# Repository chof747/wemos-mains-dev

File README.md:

## Board to combine a Wemos D1 Mini with a mini power supply

This is a small board that can take a Wemos D1 Mini  together with a 5V mini power supply to obtain a W-Lan microcontroller board with IO pins able to put e.g. in a switch box and power it
directly from mains

It contains the following elements:

- WeMos D1 Mini (or any other microcontroller board that has the same pin configuration)
- A 600mA/5V (3W) power supply 
- A 2x12 pinheader providing all GPIO Pins of the D1 mini in a suitable configuration
- Pull-Up Resistors for the SDA and SCL line
- Jumper Pins to select if the pullups should be used or not
- ByPass Capacitors for the 3V3 and GND lines in vicinity to the One-Wire and analog pin
- Screw Terminal to connect the board to mains

## Features

The breakout of the pins is designed in a way that it can support HATs of a certain form factor. So far I have designed the following HATs which you can find here:

- RJ11 Socket HAT [chof747/rj11-wemos-hat](https://github.com/chof747/rj11-wemos-hat)

## Revision History:

- **v1.0**: Initial version (filed for fabrication: 19.04.2023)
- **v1.1**: Revision 1 with corrected orientation of power supply and reduced ground plane to avoid collision with high voltage (filed for fabrication: 17.7.2023; First Assembly 06.10.2023)

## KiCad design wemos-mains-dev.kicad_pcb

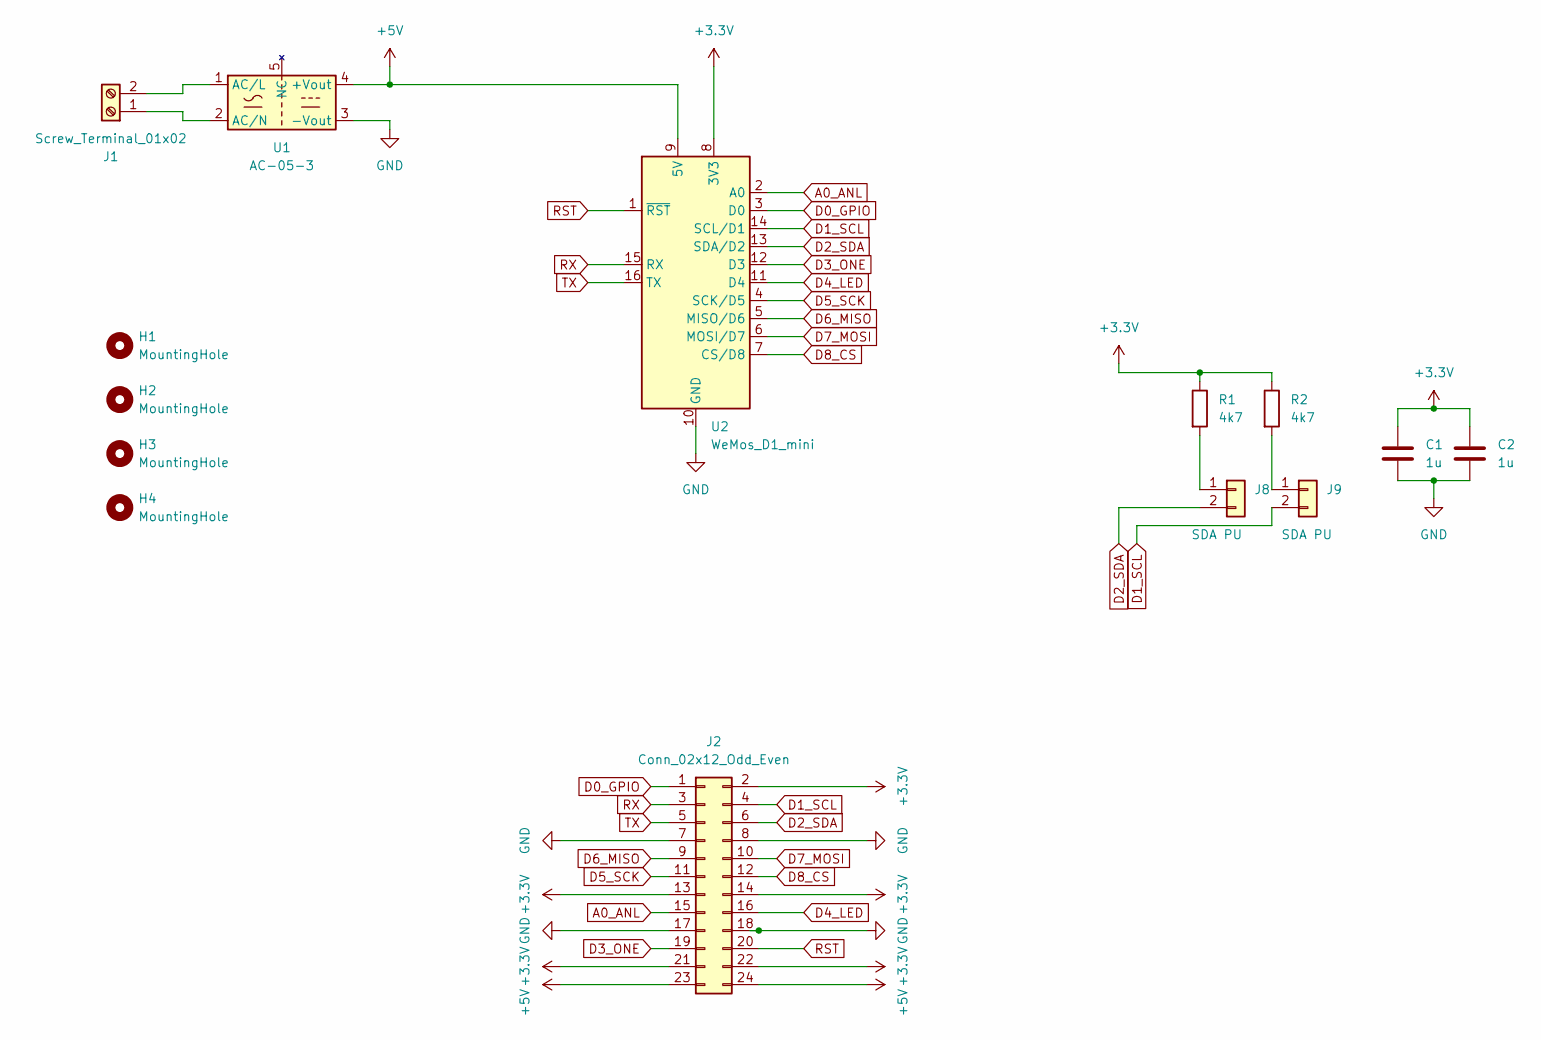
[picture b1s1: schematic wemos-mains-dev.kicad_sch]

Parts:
C1, C2: 1u; C_0603_1608Metric_Pad1.08x0.95mm_HandSolder
H1, H2, H3, H4: MountingHole; MountingHole_3.2mm_M3-smallBorder
J1: Screw_Terminal_01x02; TerminalBlock_bornier-2_P5.08mm
J2: Conn_02x12_Odd_Even; PinSocket_2x12_P2.54mm_Vertical
J8, J9: SDA PU; PinHeader_1x02_P2.54mm_Vertical
R1, R2: 4k7; R_0603_1608Metric_Pad0.98x0.95mm_HandSolder
U1: AC-05-3; AZDelivery AC-05-3
U2: WeMos_D1_mini; WEMOS_D1_mini_light

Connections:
+3.3V: C1.1, C2.1, J2.2, J2.13, J2.14, J2.21, J2.22, R1.1, R2.1, U2.8 (3V3)
+5V: J2.23, J2.24, U1.4 (+Vout), U2.9 (5V)
A0_ANL: J2.15, U2.2 (A0)
D0_GPIO: J2.1, U2.3 (D0)
D1_SCL: J2.4, J9.2, U2.14 (SCL/D1)
D2_SDA: J2.6, J8.2, U2.13 (SDA/D2)
D3_ONE: J2.19, U2.12 (D3)
D4_LED: J2.16, U2.11 (D4)
D5_SCK: J2.11, U2.4 (SCK/D5)
D6_MISO: J2.9, U2.5 (MISO/D6)
D7_MOSI: J2.10, U2.6 (MOSI/D7)
D8_CS: J2.12, U2.7 (CS/D8)
GND: C1.2, C2.2, J2.7, J2.8, J2.17, J2.18, U1.3 (-Vout), U2.10 (GND)
unnamed: J1.1, U1.2 (AC/N)
unnamed: J1.2, U1.1 (AC/L)
unnamed: J8.1, R1.2
unnamed: J9.1, R2.2
RST: J2.20, U2.1 (~RST)
RX: J2.3, U2.15 (RX)
TX: J2.5, U2.16 (TX)

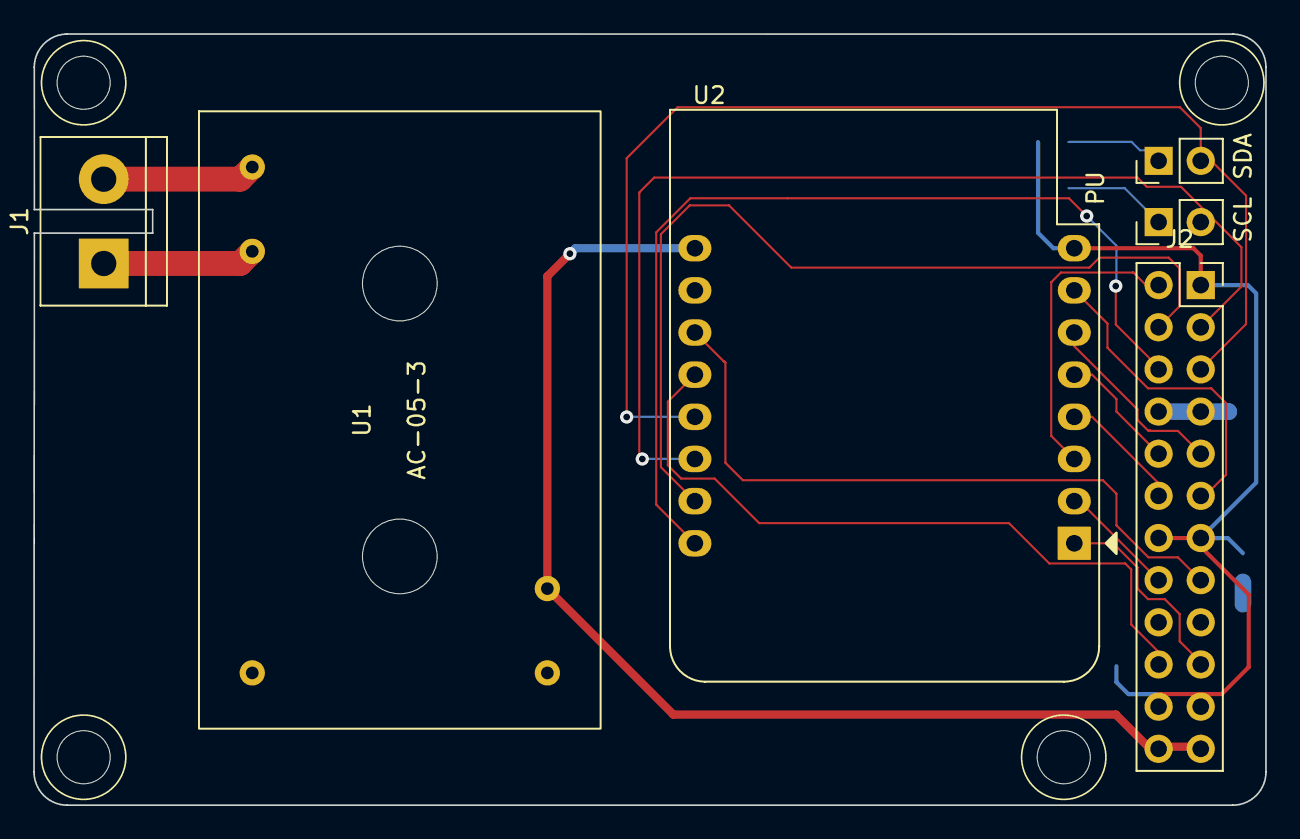
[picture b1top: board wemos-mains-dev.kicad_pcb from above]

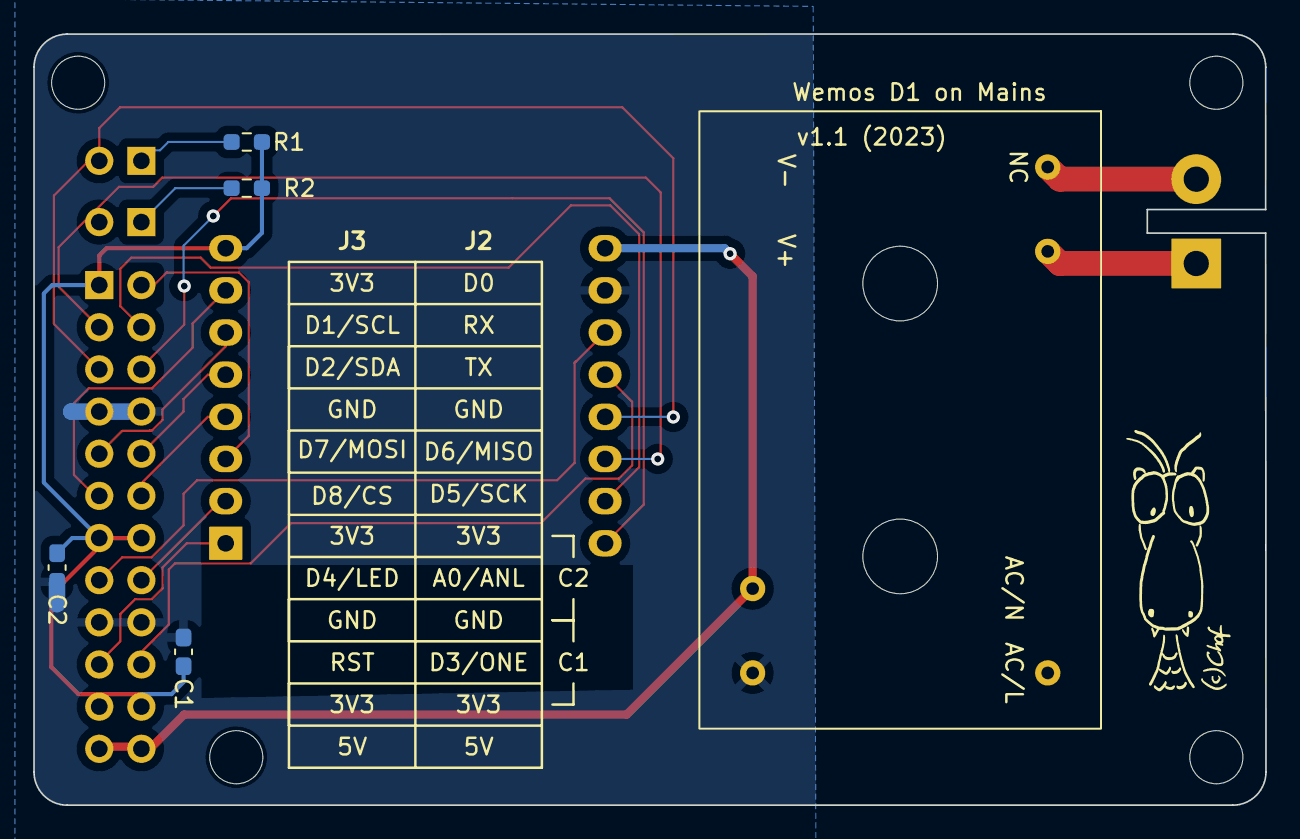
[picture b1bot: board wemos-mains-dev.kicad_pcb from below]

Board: 2 copper layers, 74.2 x 46.5 mm, 14 parts (4 on the bottom side), 20 nets.

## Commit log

2023-04-19 Version 1.0 including basic set of features for first PT board
2023-04-20 Changed pinheader for breakout to 02x12
2023-04-20 Added step file to .gitignore
2023-04-20 Revision 1 commit
    - Added suitable README file
    - Minor updates on board regarding Front Fab layer (no impact on board)
2023-04-27 Updated template for KiCAD 7
2023-05-04 Corrections for rev. 1
    - Corrected orientation of power supply footprint
    - Reduced ground plane to low voltage side
2023-05-31 updated warnings
2023-07-11 made a space between high volt contacts
2023-08-03 Added fabrication date of revision 1.1
2023-10-06 First Assembly rev. 1.1
2024-02-07 Added reference to RJ11 HAT
2024-02-10 changed hat socket to socket from header
